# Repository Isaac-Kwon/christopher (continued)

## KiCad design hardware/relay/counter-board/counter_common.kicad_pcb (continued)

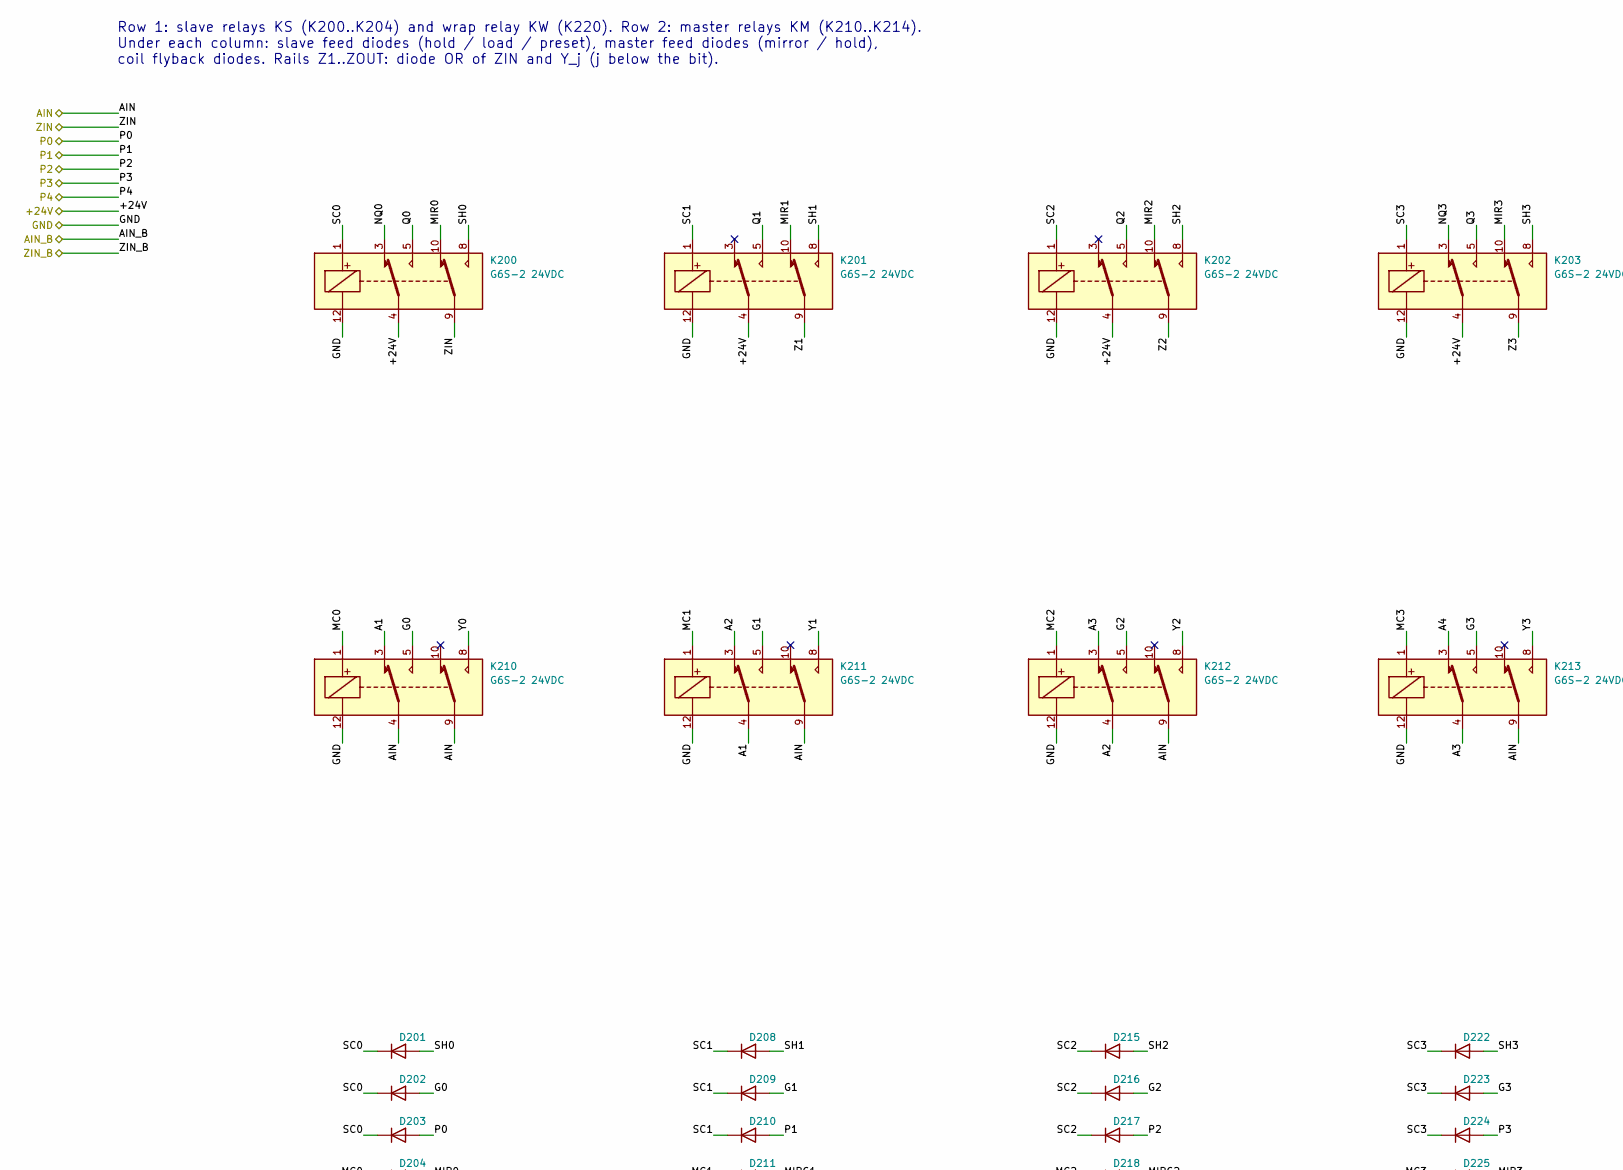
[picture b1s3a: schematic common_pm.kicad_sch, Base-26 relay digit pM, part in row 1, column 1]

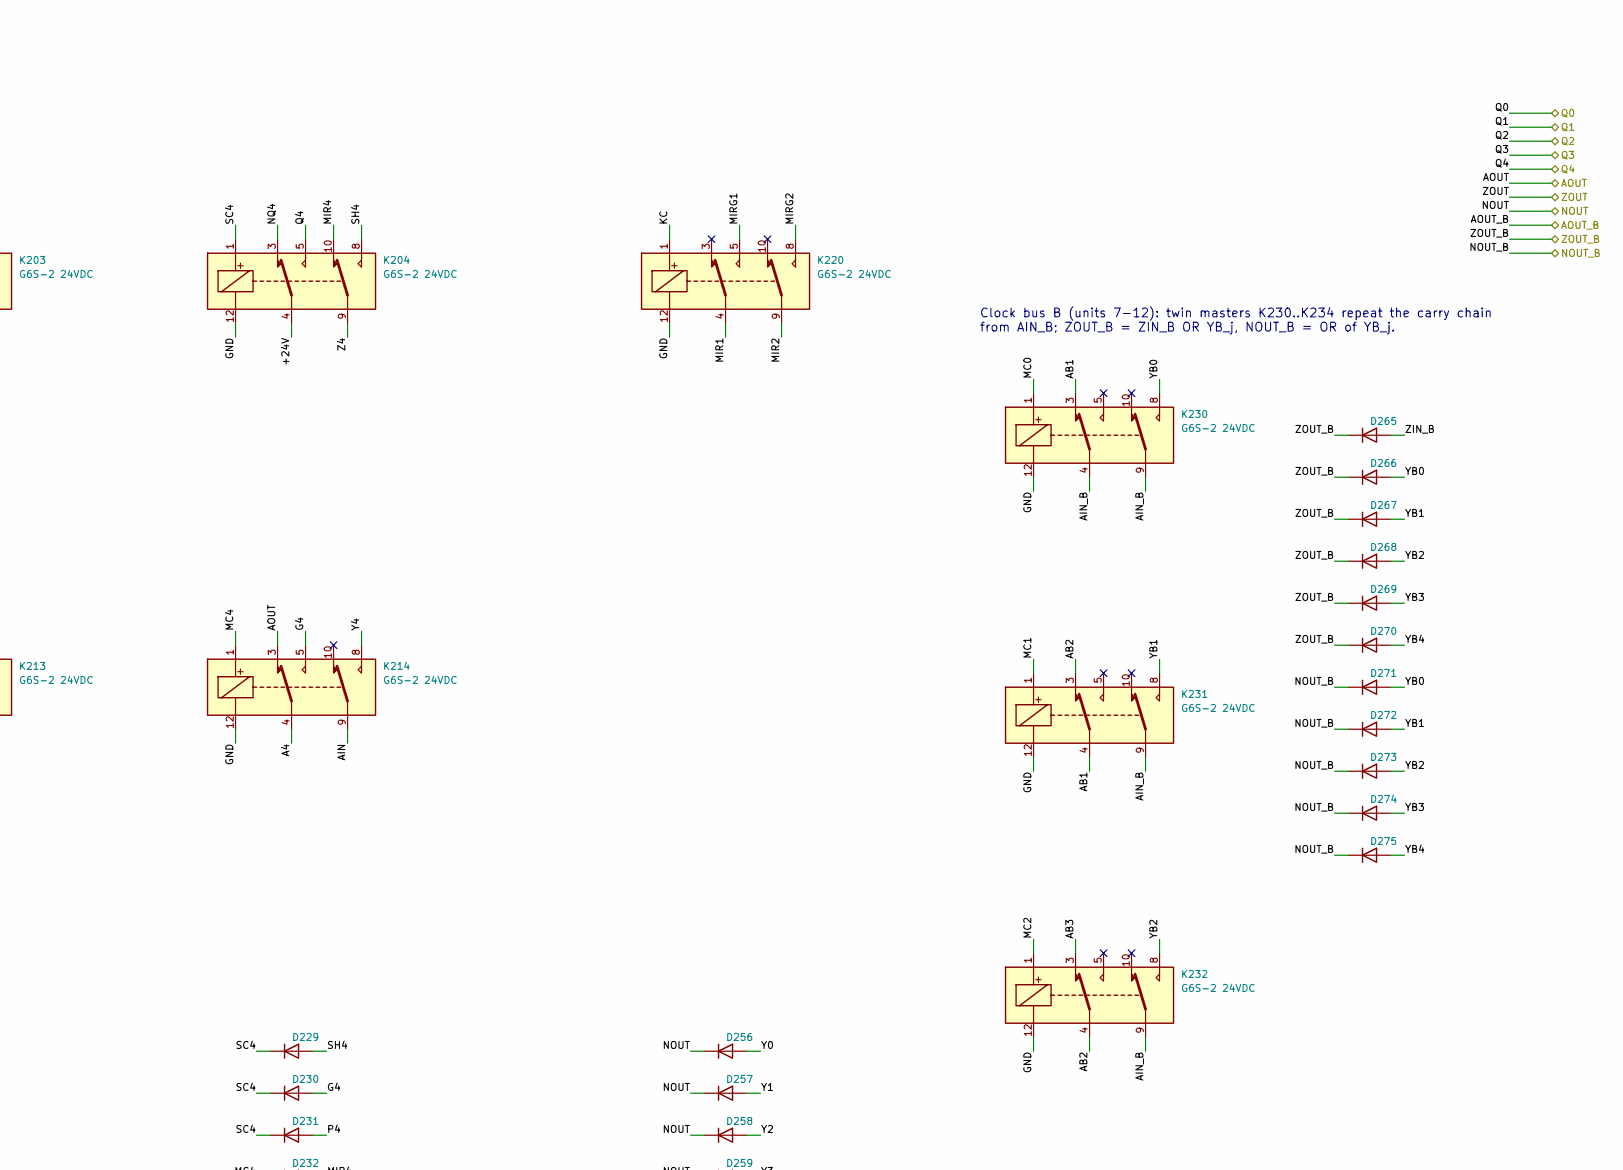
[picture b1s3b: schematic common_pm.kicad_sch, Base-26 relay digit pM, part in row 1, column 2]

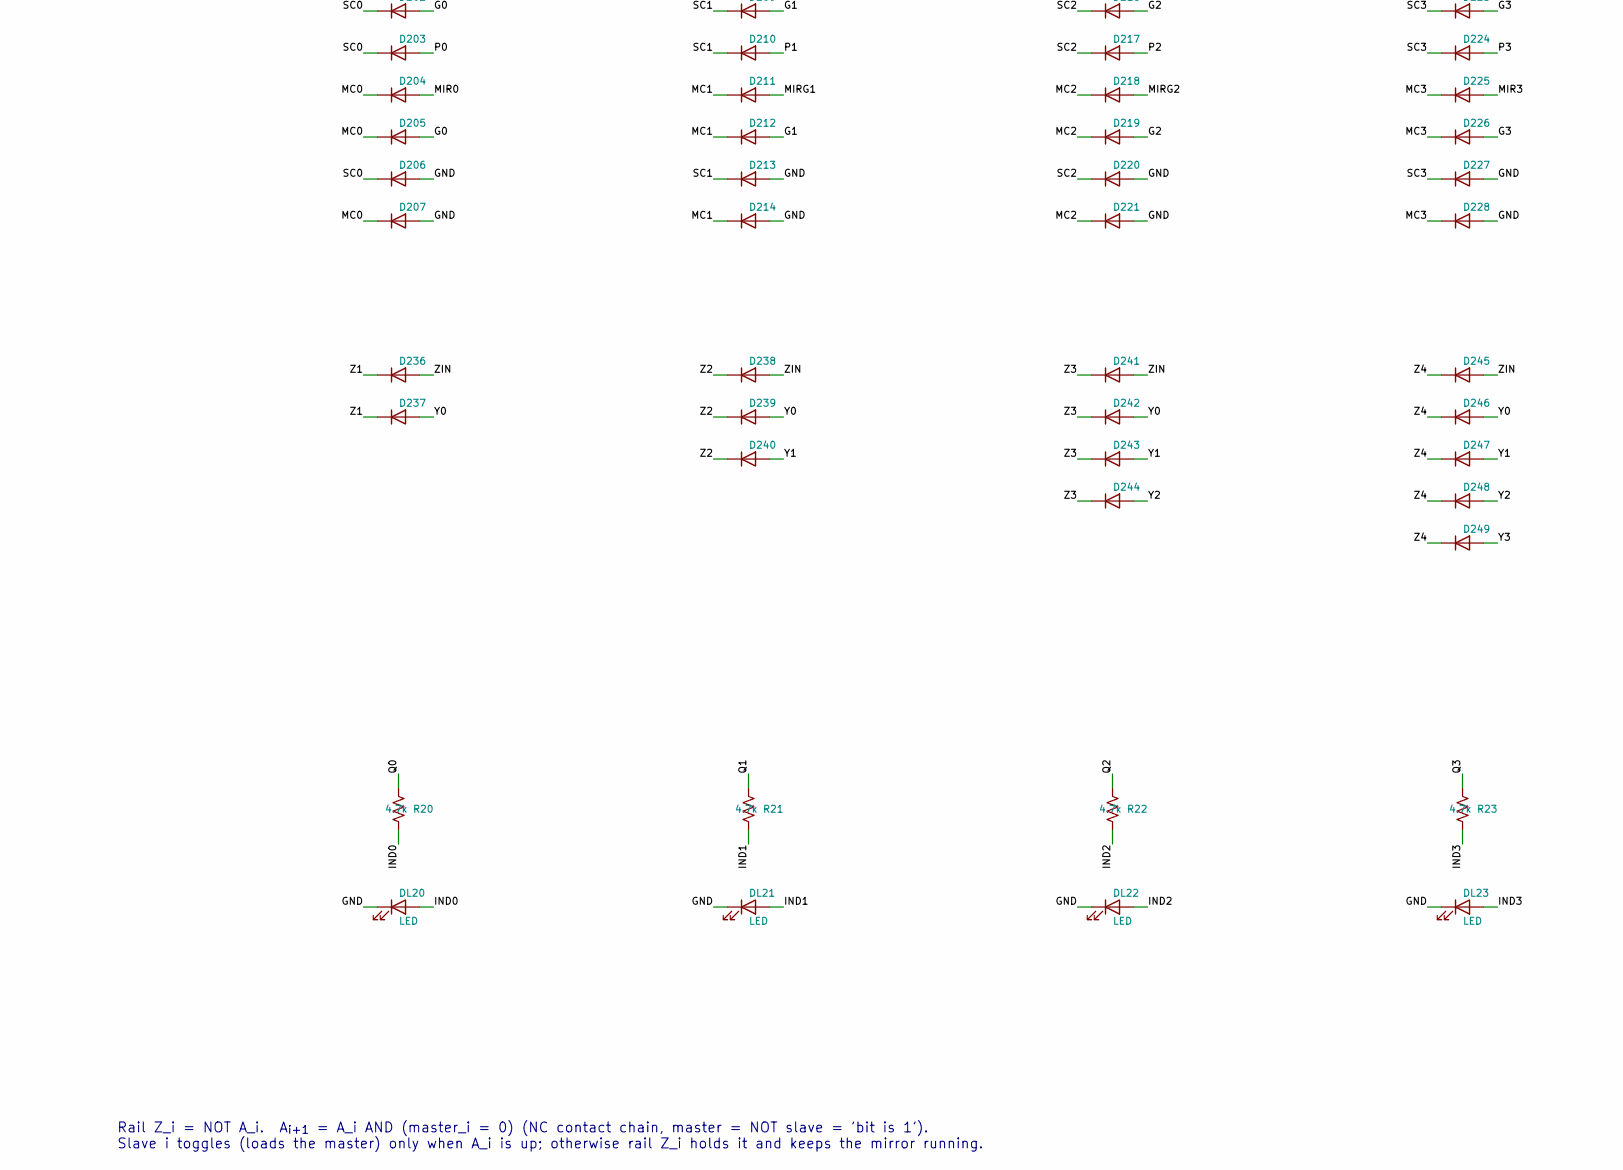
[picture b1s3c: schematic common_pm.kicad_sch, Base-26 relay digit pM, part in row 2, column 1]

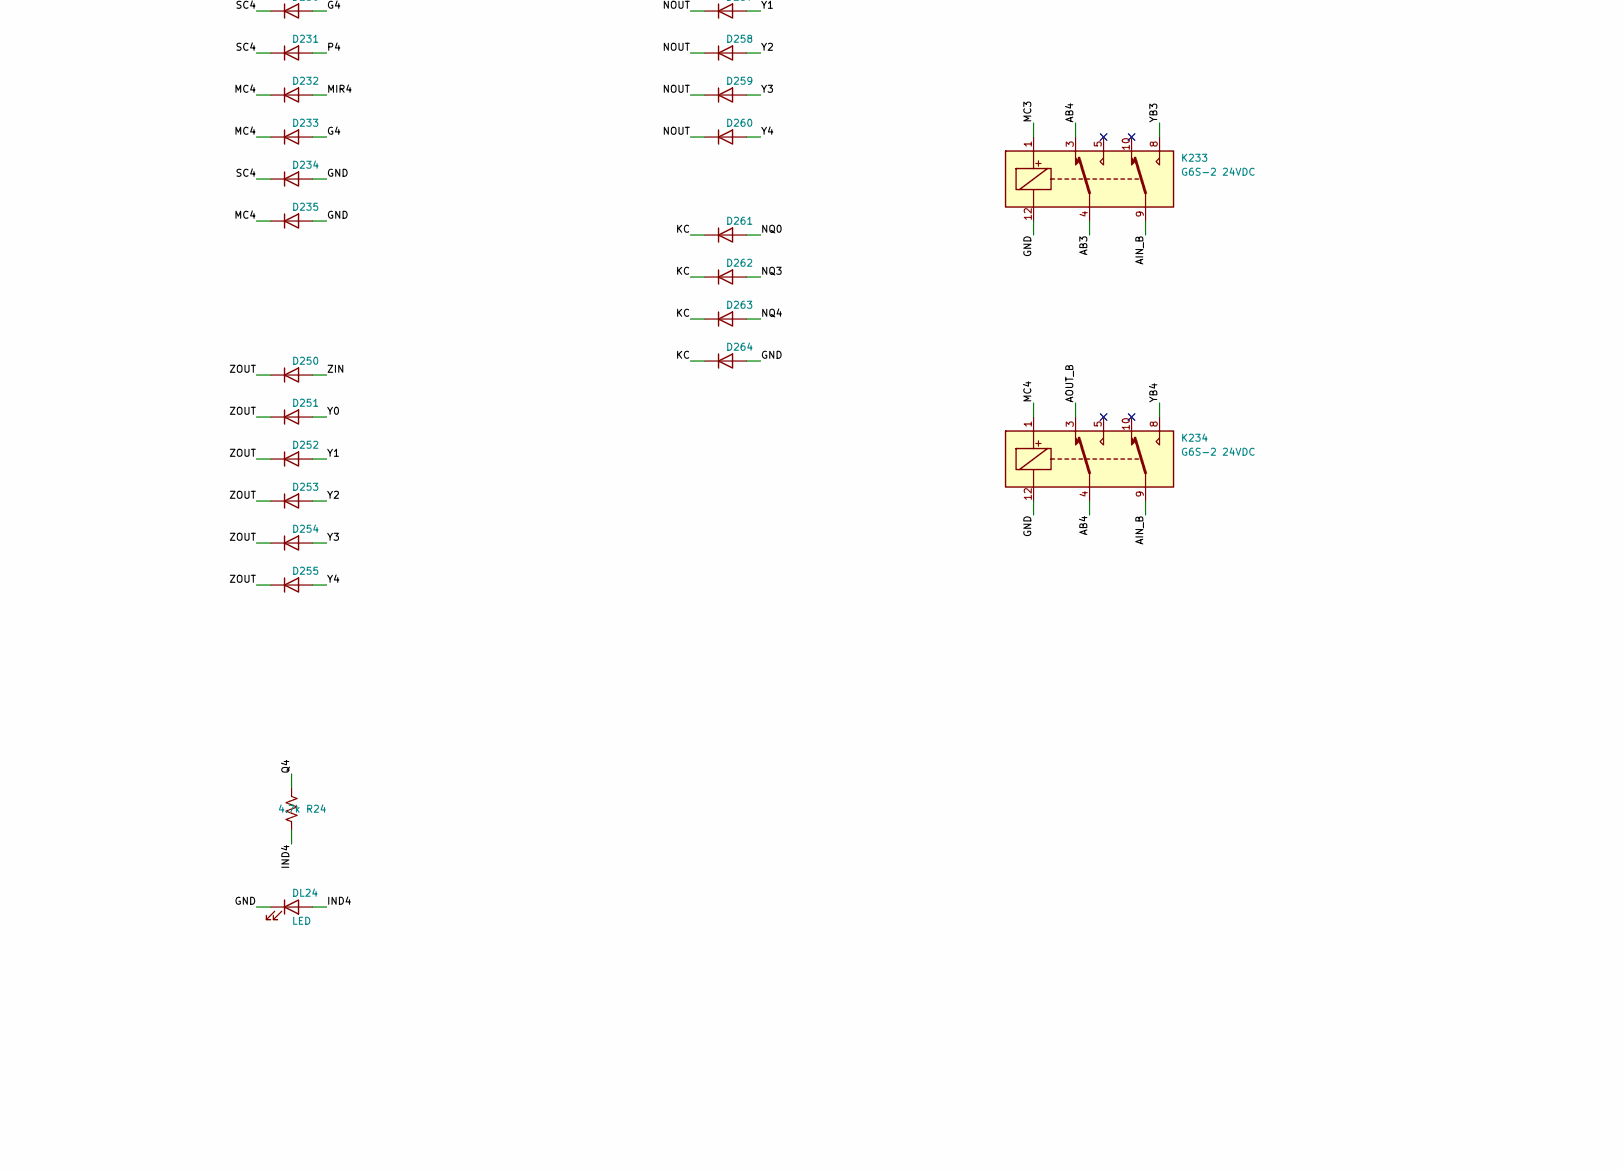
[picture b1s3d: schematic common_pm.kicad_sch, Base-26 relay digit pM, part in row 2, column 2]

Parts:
D201, D202, D203, D204, D205, D208, D209, D210, D211, D212, D215, D216, D217, D218, D219, D222, D223, D224, D225, D226, D229, D230, D231, D232, D233, D236, D237, D238, D239, D240, D241, D242, D243, D244, D245, D246, D247, D248, D249, D250, D251, D252, D253, D254, D255, D256, D257, D258, D259, D260, D261, D262, D263, D265, D266, D267, D268, D269, D270, D271, D272, D273, D274, D275: 1N5819W; D_SOD-123
D206, D207, D213, D214, D220, D221, D227, D228, D234, D235, D264: 1N4148W; D_SOD-123
DL20, DL21, DL22, DL23, DL24: LED; LED_0603_1608Metric
K200, K201, K202, K203, K204, K210, K211, K212, K213, K214, K220, K230, K231, K232, K233, K234: G6S-2 24VDC; Relay_DPDT_Omron_G6S-2
R20, R21, R22, R23, R24: 4.7k; R_0603_1608Metric

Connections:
/+24V: K200.4, K201.4, K202.4, K203.4, K204.4; also elsewhere on the board
/A1B: K214.3; also elsewhere on the board
/A1B_B: K234.3; also elsewhere on the board
/A2B: D256.1 (K), D257.1 (K), D258.1 (K), D259.1 (K), D260.1 (K); also elsewhere on the board
/A2B_B: D271.1 (K), D272.1 (K), D273.1 (K), D274.1 (K), D275.1 (K); also elsewhere on the board
/DIGIT_PM/A1: K210.3, K211.4
/DIGIT_PM/A2: K211.3, K212.4
/DIGIT_PM/A3: K212.3, K213.4
/DIGIT_PM/A4: K213.3, K214.4
/DIGIT_PM/AB1: K230.3, K231.4
/DIGIT_PM/AB2: K231.3, K232.4
/DIGIT_PM/AB3: K232.3, K233.4
/DIGIT_PM/AB4: K233.3, K234.4
/DIGIT_PM/G0: D202.2 (A), D205.2 (A), K210.5
/DIGIT_PM/G1: D209.2 (A), D212.2 (A), K211.5
/DIGIT_PM/G2: D216.2 (A), D219.2 (A), K212.5
/DIGIT_PM/G3: D223.2 (A), D226.2 (A), K213.5
/DIGIT_PM/G4: D230.2 (A), D233.2 (A), K214.5
/DIGIT_PM/IND0: DL20.2 (A), R20.2
/DIGIT_PM/IND1: DL21.2 (A), R21.2
/DIGIT_PM/IND2: DL22.2 (A), R22.2
/DIGIT_PM/IND3: DL23.2 (A), R23.2
/DIGIT_PM/IND4: DL24.2 (A), R24.2
/DIGIT_PM/KC: D261.1 (K), D262.1 (K), D263.1 (K), D264.1 (K), K220.1
/DIGIT_PM/MC0: D204.1 (K), D205.1 (K), D207.1 (K), K210.1, K230.1
/DIGIT_PM/MC1: D211.1 (K), D212.1 (K), D214.1 (K), K211.1, K231.1
/DIGIT_PM/MC2: D218.1 (K), D219.1 (K), D221.1 (K), K212.1, K232.1
/DIGIT_PM/MC3: D225.1 (K), D226.1 (K), D228.1 (K), K213.1, K233.1
/DIGIT_PM/MC4: D232.1 (K), D233.1 (K), D235.1 (K), K214.1, K234.1
/DIGIT_PM/MIR0: D204.2 (A), K200.10
/DIGIT_PM/MIR1: K201.10, K220.4
/DIGIT_PM/MIR2: K202.10, K220.9
/DIGIT_PM/MIR3: D225.2 (A), K203.10
/DIGIT_PM/MIR4: D232.2 (A), K204.10
/DIGIT_PM/MIRG1: D211.2 (A), K220.5
/DIGIT_PM/MIRG2: D218.2 (A), K220.8
/DIGIT_PM/NQ0: D261.2 (A), K200.3
/DIGIT_PM/NQ3: D262.2 (A), K203.3
/DIGIT_PM/NQ4: D263.2 (A), K204.3
/DIGIT_PM/SC0: D201.1 (K), D202.1 (K), D203.1 (K), D206.1 (K), K200.1
/DIGIT_PM/SC1: D208.1 (K), D209.1 (K), D210.1 (K), D213.1 (K), K201.1
/DIGIT_PM/SC2: D215.1 (K), D216.1 (K), D217.1 (K), D220.1 (K), K202.1
/DIGIT_PM/SC3: D222.1 (K), D223.1 (K), D224.1 (K), D227.1 (K), K203.1
/DIGIT_PM/SC4: D229.1 (K), D230.1 (K), D231.1 (K), D234.1 (K), K204.1
/DIGIT_PM/SH0: D201.2 (A), K200.8
/DIGIT_PM/SH1: D208.2 (A), K201.8
/DIGIT_PM/SH2: D215.2 (A), K202.8
/DIGIT_PM/SH3: D222.2 (A), K203.8
/DIGIT_PM/SH4: D229.2 (A), K204.8
/DIGIT_PM/Y0: D237.2 (A), D239.2 (A), D242.2 (A), D246.2 (A), D251.2 (A), D256.2 (A), K210.8
/DIGIT_PM/Y1: D240.2 (A), D243.2 (A), D247.2 (A), D252.2 (A), D257.2 (A), K211.8
/DIGIT_PM/Y2: D244.2 (A), D248.2 (A), D253.2 (A), D258.2 (A), K212.8
/DIGIT_PM/Y3: D249.2 (A), D254.2 (A), D259.2 (A), K213.8
/DIGIT_PM/Y4: D255.2 (A), D260.2 (A), K214.8
/DIGIT_PM/YB0: D266.2 (A), D271.2 (A), K230.8
/DIGIT_PM/YB1: D267.2 (A), D272.2 (A), K231.8
/DIGIT_PM/YB2: D268.2 (A), D273.2 (A), K232.8
/DIGIT_PM/YB3: D269.2 (A), D274.2 (A), K233.8
/DIGIT_PM/YB4: D270.2 (A), D275.2 (A), K234.8
/DIGIT_PM/Z1: D236.1 (K), D237.1 (K), K201.9
/DIGIT_PM/Z2: D238.1 (K), D239.1 (K), D240.1 (K), K202.9
/DIGIT_PM/Z3: D241.1 (K), D242.1 (K), D243.1 (K), D244.1 (K), K203.9
/DIGIT_PM/Z4: D245.1 (K), D246.1 (K), D247.1 (K), D248.1 (K), D249.1 (K), K204.9
/GND: D203.2 (A), D206.2 (A), D207.2 (A), D210.2 (A), D213.2 (A), D214.2 (A), D217.2 (A), D220.2 (A), D221.2 (A), D224.2 (A), D227.2 (A), D228.2 (A), D231.2 (A), D234.2 (A), D235.2 (A), D264.2 (A), DL20.1 (K), DL21.1 (K), DL22.1 (K), DL23.1 (K), DL24.1 (K), K200.12, K201.12, K202.12, K203.12, K204.12, K210.12, K211.12, K212.12, K213.12, K214.12, K220.12, K230.12, K231.12, K232.12, K233.12, K234.12; also elsewhere on the board
/LC: K210.4, K210.9, K211.9, K212.9, K213.9, K214.9; also elsewhere on the board
/LC_B: K230.4, K230.9, K231.9, K232.9, K233.9, K234.9; also elsewhere on the board
/M0: K200.5, R20.1; also elsewhere on the board
/M1: K201.5, R21.1; also elsewhere on the board
/M2: K202.5, R22.1; also elsewhere on the board
/M3: K203.5, R23.1; also elsewhere on the board
/M4: K204.5, R24.1; also elsewhere on the board
/Z1B: D250.1 (K), D251.1 (K), D252.1 (K), D253.1 (K), D254.1 (K), D255.1 (K); also elsewhere on the board
/Z1B_B: D265.1 (K), D266.1 (K), D267.1 (K), D268.1 (K), D269.1 (K), D270.1 (K); also elsewhere on the board
/ZL: D236.2 (A), D238.2 (A), D241.2 (A), D245.2 (A), D250.2 (A), K200.9; also elsewhere on the board
/ZL_B: D265.2 (A); also elsewhere on the board

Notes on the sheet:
Clock bus B (units 7-12): twin masters K230..K234 repeat the carry chain from AIN_B; ZOUT_B = ZIN_B OR YB_j, NOUT_B = OR of YB_j.
Row 1: slave relays KS (K200..K204) and wrap relay KW (K220). Row 2: master relays KM (K210..K214). Under each column: slave feed diodes (hold / load / preset), master feed diodes (mirror / hold), coil flyback diodes. Rails Z1..ZOUT: diode OR of ZIN and Y_j (j below the bit).
Rail Z_i = NOT A_i. A_{i+1} = A_i AND (master_i = 0) (NC contact chain, master = NOT slave = 'bit is 1'). Slave i toggles (loads the master) only when A_i is up; otherwise rail Z_i holds it and keeps the mirror running.

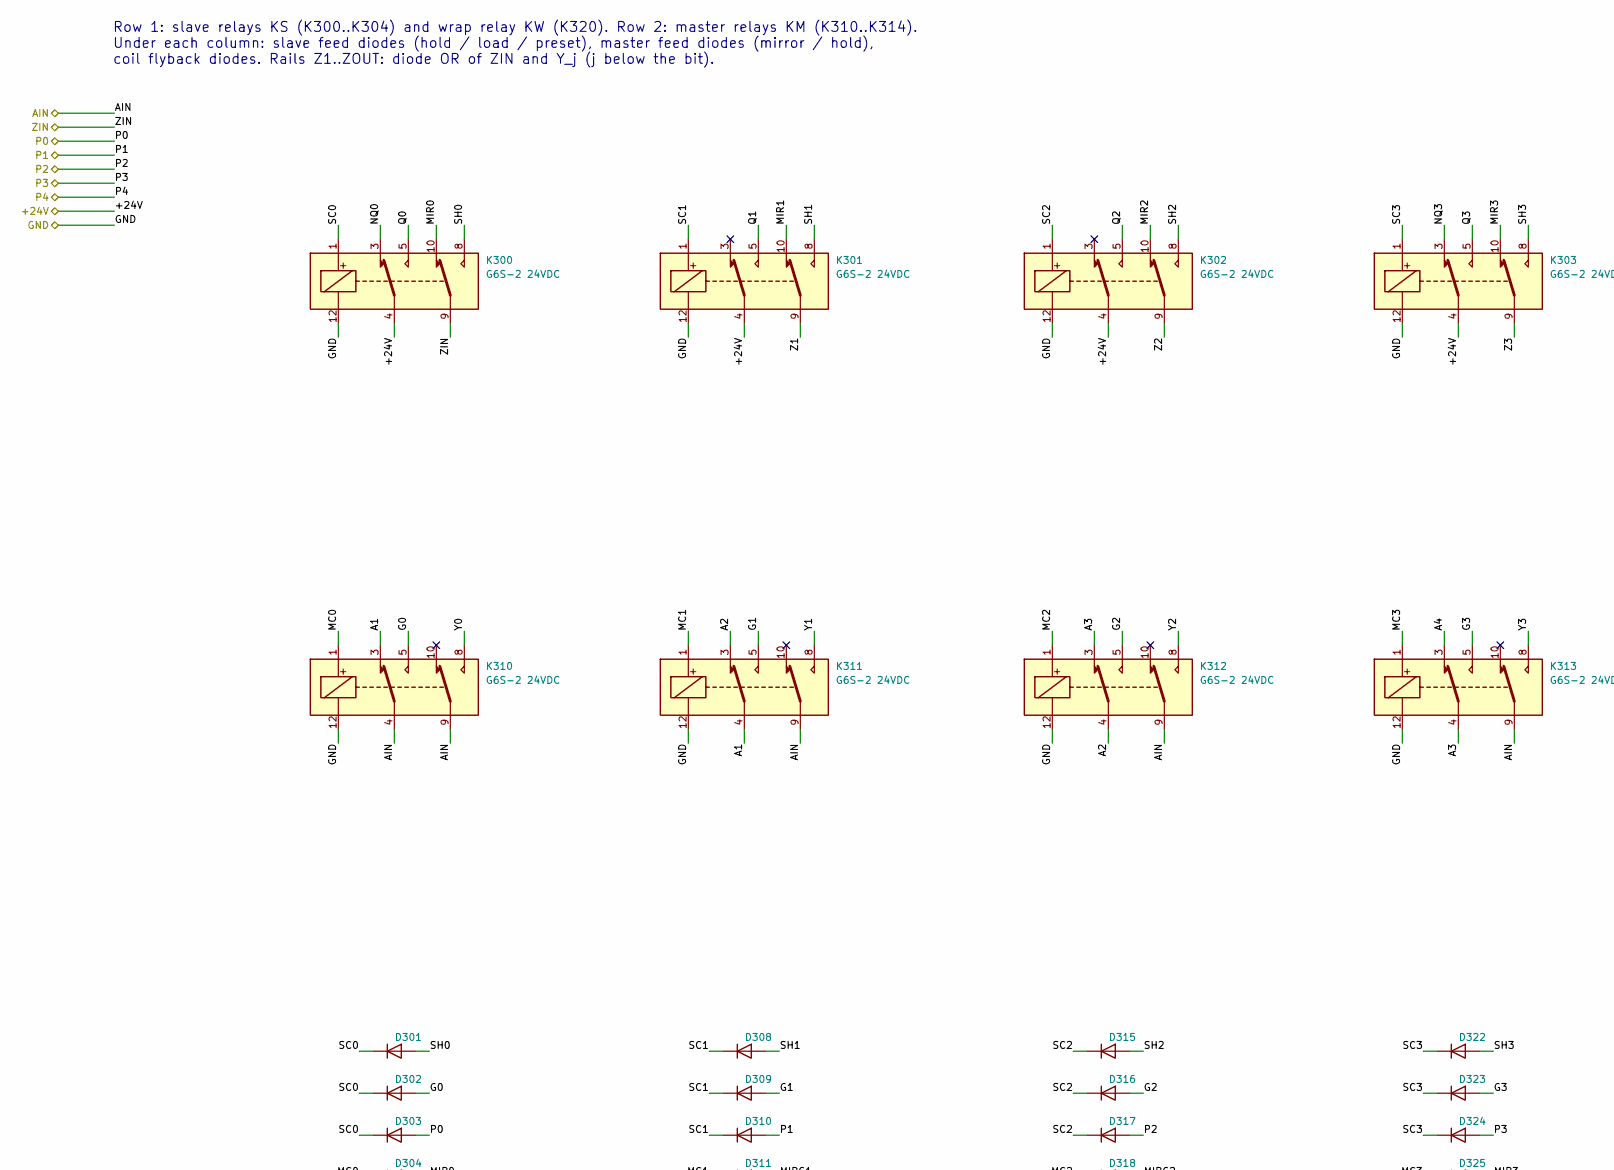
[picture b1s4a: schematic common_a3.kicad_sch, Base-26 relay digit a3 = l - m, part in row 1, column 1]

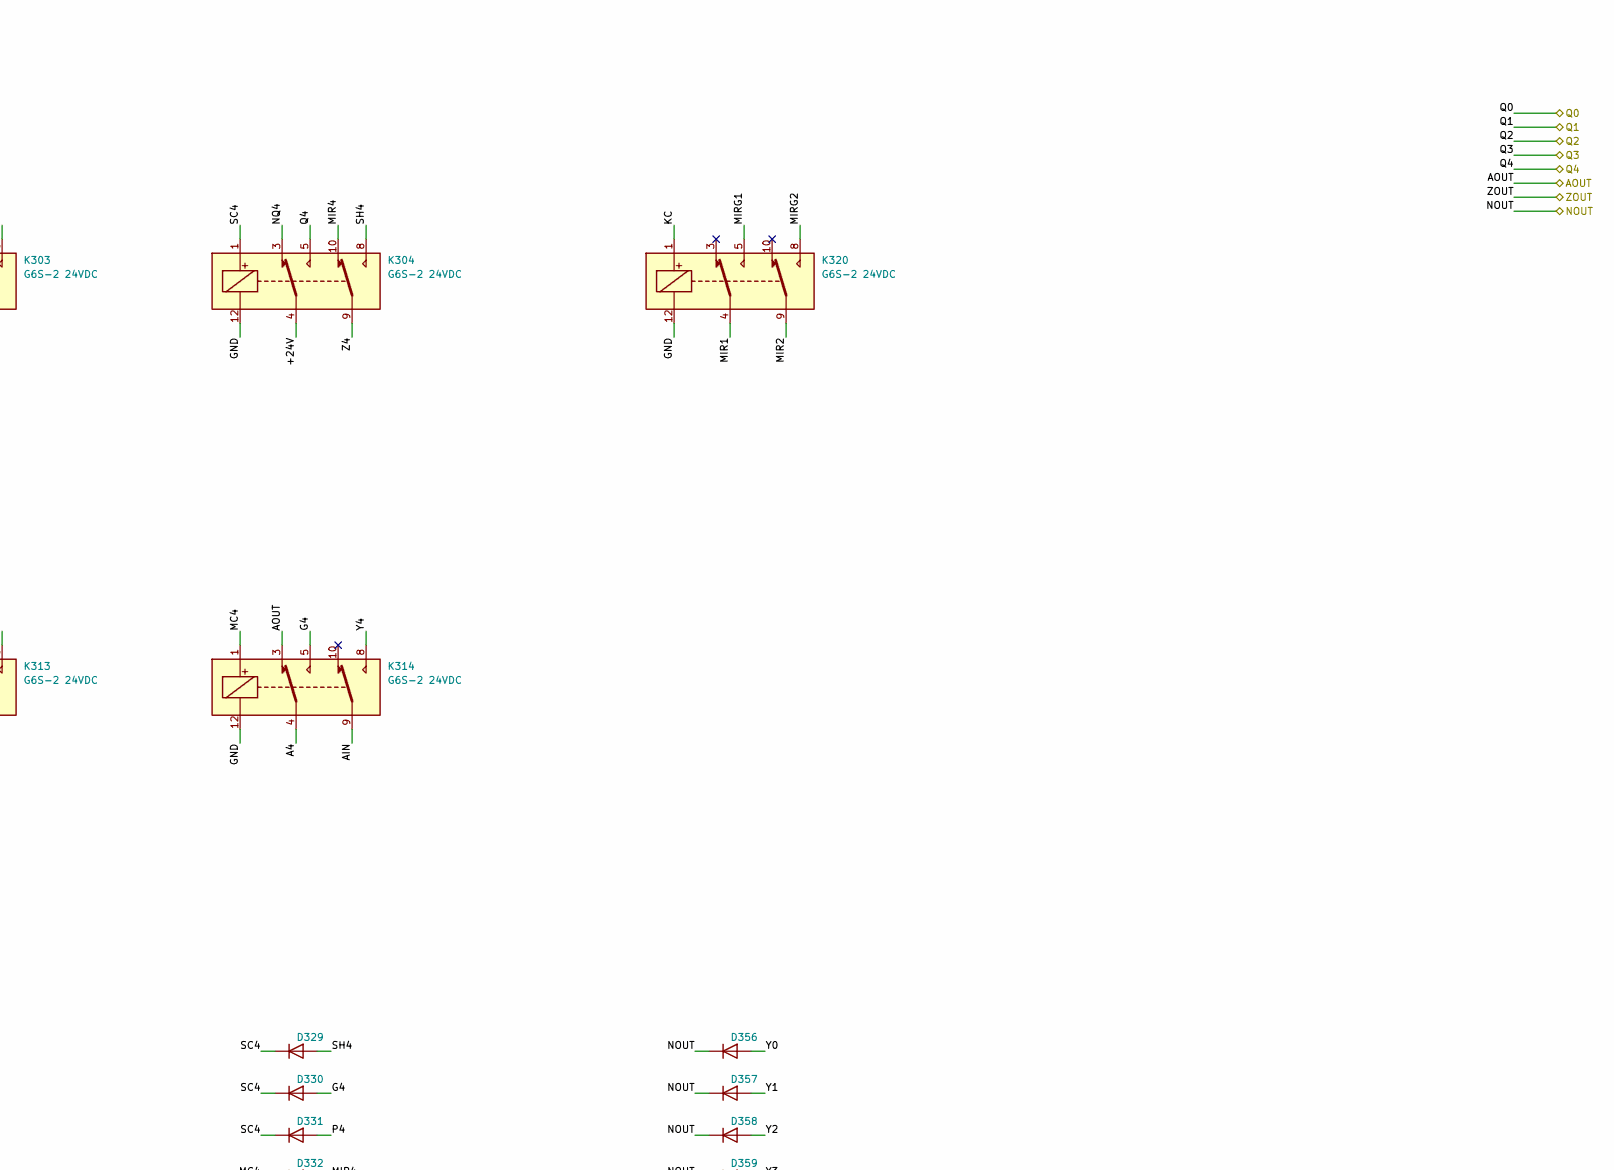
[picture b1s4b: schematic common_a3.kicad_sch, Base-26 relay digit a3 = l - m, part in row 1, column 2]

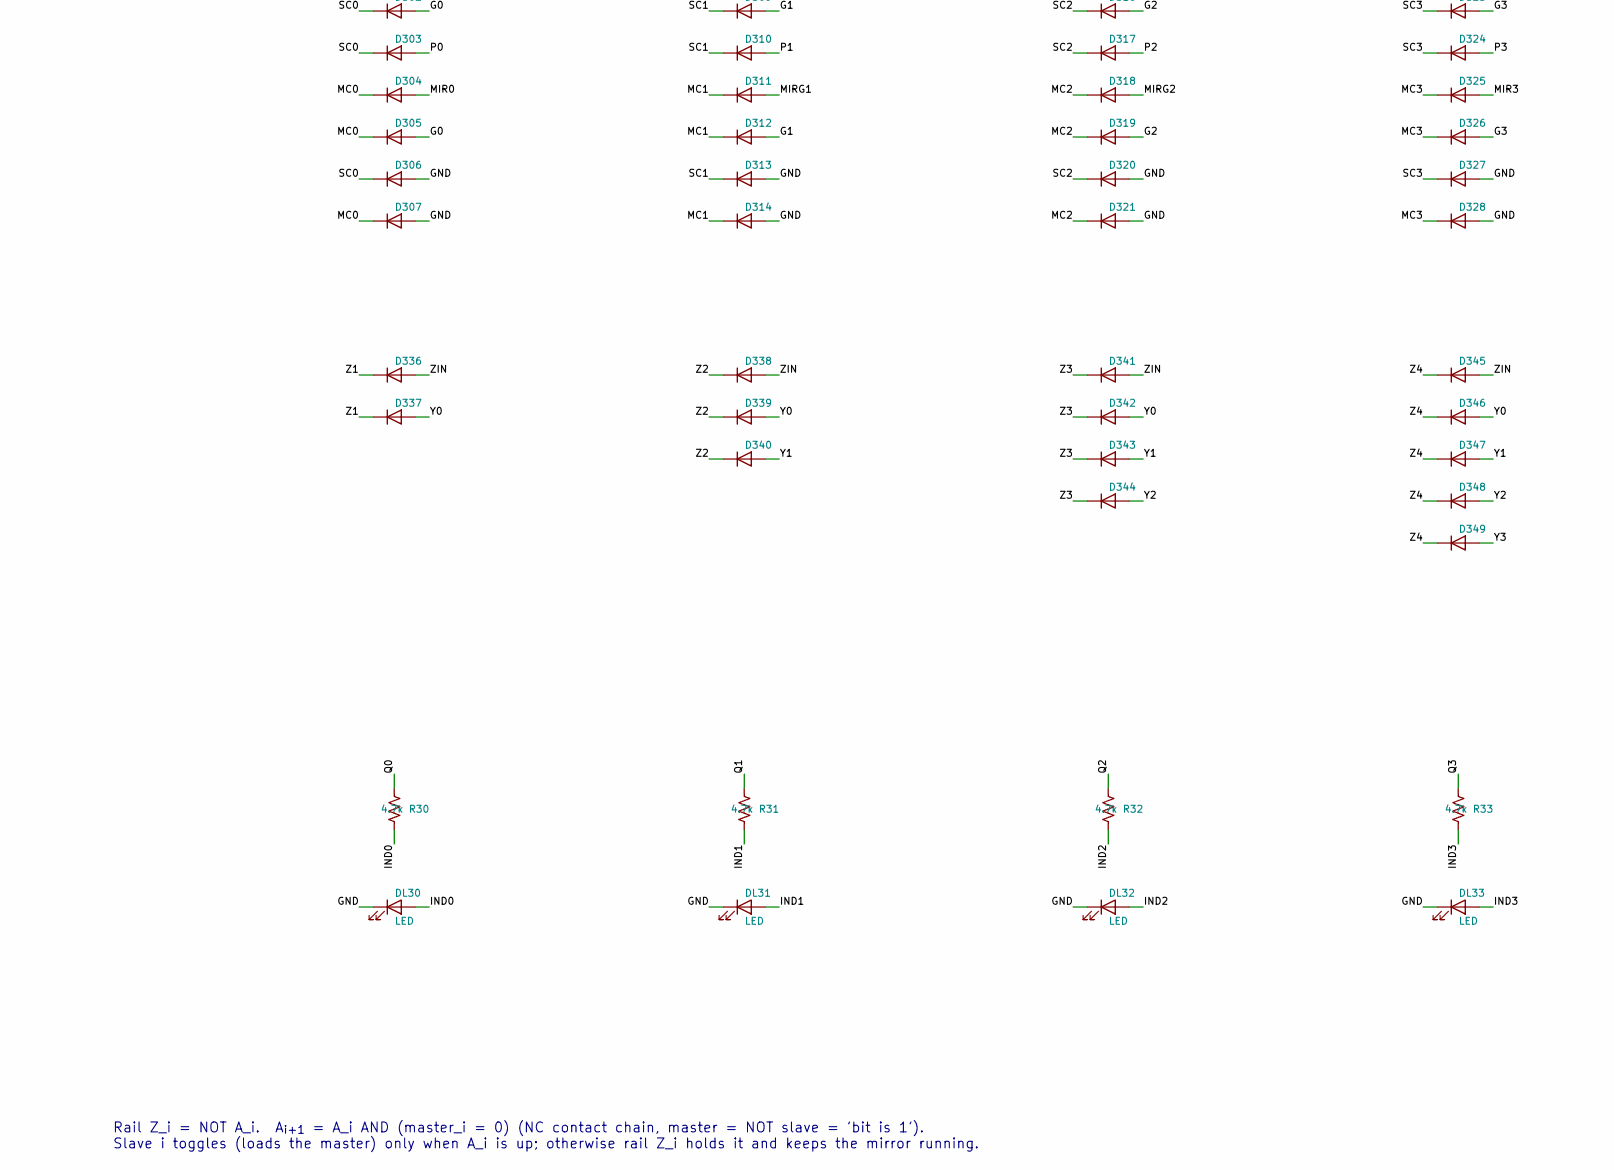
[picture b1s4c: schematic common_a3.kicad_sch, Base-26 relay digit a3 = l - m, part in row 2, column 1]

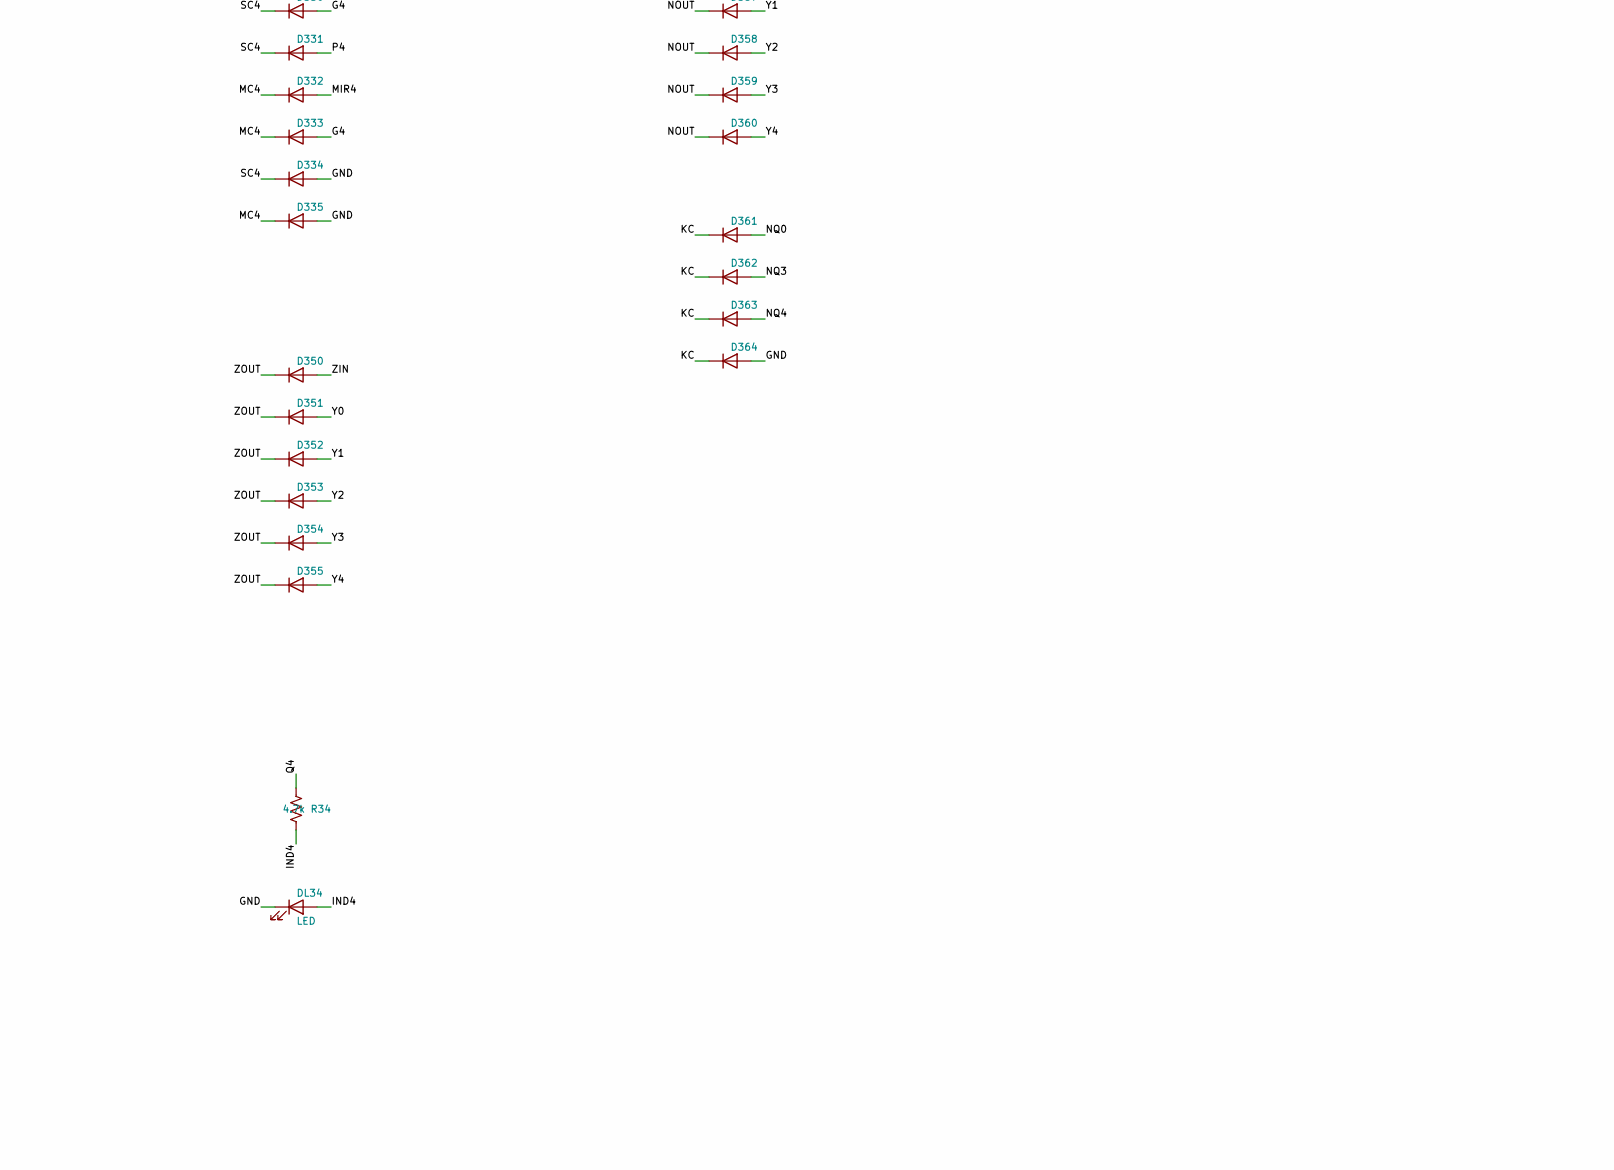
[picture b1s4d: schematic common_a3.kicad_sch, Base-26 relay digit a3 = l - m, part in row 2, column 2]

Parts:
D301, D302, D303, D304, D305, D308, D309, D310, D311, D312, D315, D316, D317, D318, D319, D322, D323, D324, D325, D326, D329, D330, D331, D332, D333, D336, D337, D338, D339, D340, D341, D342, D343, D344, D345, D346, D347, D348, D349, D350, D351, D352, D353, D354, D355, D356, D357, D358, D359, D360, D361, D362, D363: 1N5819W; D_SOD-123
D306, D307, D313, D314, D320, D321, D327, D328, D334, D335, D364: 1N4148W; D_SOD-123
DL30, DL31, DL32, DL33, DL34: LED; LED_0603_1608Metric
K300, K301, K302, K303, K304, K310, K311, K312, K313, K314, K320: G6S-2 24VDC; Relay_DPDT_Omron_G6S-2
R30, R31, R32, R33, R34: 4.7k; R_0603_1608Metric

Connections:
/+24V: K300.4, K301.4, K302.4, K303.4, K304.4; also elsewhere on the board
/DIGIT_A3/A1: K310.3, K311.4
/DIGIT_A3/A2: K311.3, K312.4
/DIGIT_A3/A3: K312.3, K313.4
/DIGIT_A3/A4: K313.3, K314.4
/DIGIT_A3/AOUT: K314.3
/DIGIT_A3/G0: D302.2 (A), D305.2 (A), K310.5
/DIGIT_A3/G1: D309.2 (A), D312.2 (A), K311.5
/DIGIT_A3/G2: D316.2 (A), D319.2 (A), K312.5
/DIGIT_A3/G3: D323.2 (A), D326.2 (A), K313.5
/DIGIT_A3/G4: D330.2 (A), D333.2 (A), K314.5
/DIGIT_A3/IND0: DL30.2 (A), R30.2
/DIGIT_A3/IND1: DL31.2 (A), R31.2
/DIGIT_A3/IND2: DL32.2 (A), R32.2
/DIGIT_A3/IND3: DL33.2 (A), R33.2
/DIGIT_A3/IND4: DL34.2 (A), R34.2
/DIGIT_A3/KC: D361.1 (K), D362.1 (K), D363.1 (K), D364.1 (K), K320.1
/DIGIT_A3/MC0: D304.1 (K), D305.1 (K), D307.1 (K), K310.1
/DIGIT_A3/MC1: D311.1 (K), D312.1 (K), D314.1 (K), K311.1
/DIGIT_A3/MC2: D318.1 (K), D319.1 (K), D321.1 (K), K312.1
/DIGIT_A3/MC3: D325.1 (K), D326.1 (K), D328.1 (K), K313.1
/DIGIT_A3/MC4: D332.1 (K), D333.1 (K), D335.1 (K), K314.1
/DIGIT_A3/MIR0: D304.2 (A), K300.10
/DIGIT_A3/MIR1: K301.10, K320.4
/DIGIT_A3/MIR2: K302.10, K320.9
/DIGIT_A3/MIR3: D325.2 (A), K303.10
/DIGIT_A3/MIR4: D332.2 (A), K304.10
/DIGIT_A3/MIRG1: D311.2 (A), K320.5
/DIGIT_A3/MIRG2: D318.2 (A), K320.8
/DIGIT_A3/NOUT: D356.1 (K), D357.1 (K), D358.1 (K), D359.1 (K), D360.1 (K)
/DIGIT_A3/NQ0: D361.2 (A), K300.3
/DIGIT_A3/NQ3: D362.2 (A), K303.3
/DIGIT_A3/NQ4: D363.2 (A), K304.3
/DIGIT_A3/SC0: D301.1 (K), D302.1 (K), D303.1 (K), D306.1 (K), K300.1
/DIGIT_A3/SC1: D308.1 (K), D309.1 (K), D310.1 (K), D313.1 (K), K301.1
/DIGIT_A3/SC2: D315.1 (K), D316.1 (K), D317.1 (K), D320.1 (K), K302.1
/DIGIT_A3/SC3: D322.1 (K), D323.1 (K), D324.1 (K), D327.1 (K), K303.1
/DIGIT_A3/SC4: D329.1 (K), D330.1 (K), D331.1 (K), D334.1 (K), K304.1
/DIGIT_A3/SH0: D301.2 (A), K300.8
/DIGIT_A3/SH1: D308.2 (A), K301.8
/DIGIT_A3/SH2: D315.2 (A), K302.8
/DIGIT_A3/SH3: D322.2 (A), K303.8
/DIGIT_A3/SH4: D329.2 (A), K304.8
/DIGIT_A3/Y0: D337.2 (A), D339.2 (A), D342.2 (A), D346.2 (A), D351.2 (A), D356.2 (A), K310.8
/DIGIT_A3/Y1: D340.2 (A), D343.2 (A), D347.2 (A), D352.2 (A), D357.2 (A), K311.8
/DIGIT_A3/Y2: D344.2 (A), D348.2 (A), D353.2 (A), D358.2 (A), K312.8
/DIGIT_A3/Y3: D349.2 (A), D354.2 (A), D359.2 (A), K313.8
/DIGIT_A3/Y4: D355.2 (A), D360.2 (A), K314.8
/DIGIT_A3/Z1: D336.1 (K), D337.1 (K), K301.9
/DIGIT_A3/Z2: D338.1 (K), D339.1 (K), D340.1 (K), K302.9
/DIGIT_A3/Z3: D341.1 (K), D342.1 (K), D343.1 (K), D344.1 (K), K303.9
/DIGIT_A3/Z4: D345.1 (K), D346.1 (K), D347.1 (K), D348.1 (K), D349.1 (K), K304.9
/DIGIT_A3/ZOUT: D350.1 (K), D351.1 (K), D352.1 (K), D353.1 (K), D354.1 (K), D355.1 (K)
/GND: D303.2 (A), D306.2 (A), D307.2 (A), D310.2 (A), D313.2 (A), D314.2 (A), D317.2 (A), D320.2 (A), D321.2 (A), D324.2 (A), D327.2 (A), D328.2 (A), D331.2 (A), D334.2 (A), D335.2 (A), D364.2 (A), DL30.1 (K), DL31.1 (K), DL32.1 (K), DL33.1 (K), DL34.1 (K), K300.12, K301.12, K302.12, K303.12, K304.12, K310.12, K311.12, K312.12, K313.12, K314.12, K320.12; also elsewhere on the board
/NL: K310.4, K310.9, K311.9, K312.9, K313.9, K314.9; also elsewhere on the board
/T0: K300.5, R30.1; also elsewhere on the board
/T1: K301.5, R31.1; also elsewhere on the board
/T2: K302.5, R32.1; also elsewhere on the board
/T3: K303.5, R33.1; also elsewhere on the board
/T4: K304.5, R34.1; also elsewhere on the board
/Z3I: D336.2 (A), D338.2 (A), D341.2 (A), D345.2 (A), D350.2 (A), K300.9; also elsewhere on the board

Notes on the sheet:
Row 1: slave relays KS (K300..K304) and wrap relay KW (K320). Row 2: master relays KM (K310..K314). Under each column: slave feed diodes (hold / load / preset), master feed diodes (mirror / hold), coil flyback diodes. Rails Z1..ZOUT: diode OR of ZIN and Y_j (j below the bit).
Rail Z_i = NOT A_i. A_{i+1} = A_i AND (master_i = 0) (NC contact chain, master = NOT slave = 'bit is 1'). Slave i toggles (loads the master) only when A_i is up; otherwise rail Z_i holds it and keeps the mirror running.
